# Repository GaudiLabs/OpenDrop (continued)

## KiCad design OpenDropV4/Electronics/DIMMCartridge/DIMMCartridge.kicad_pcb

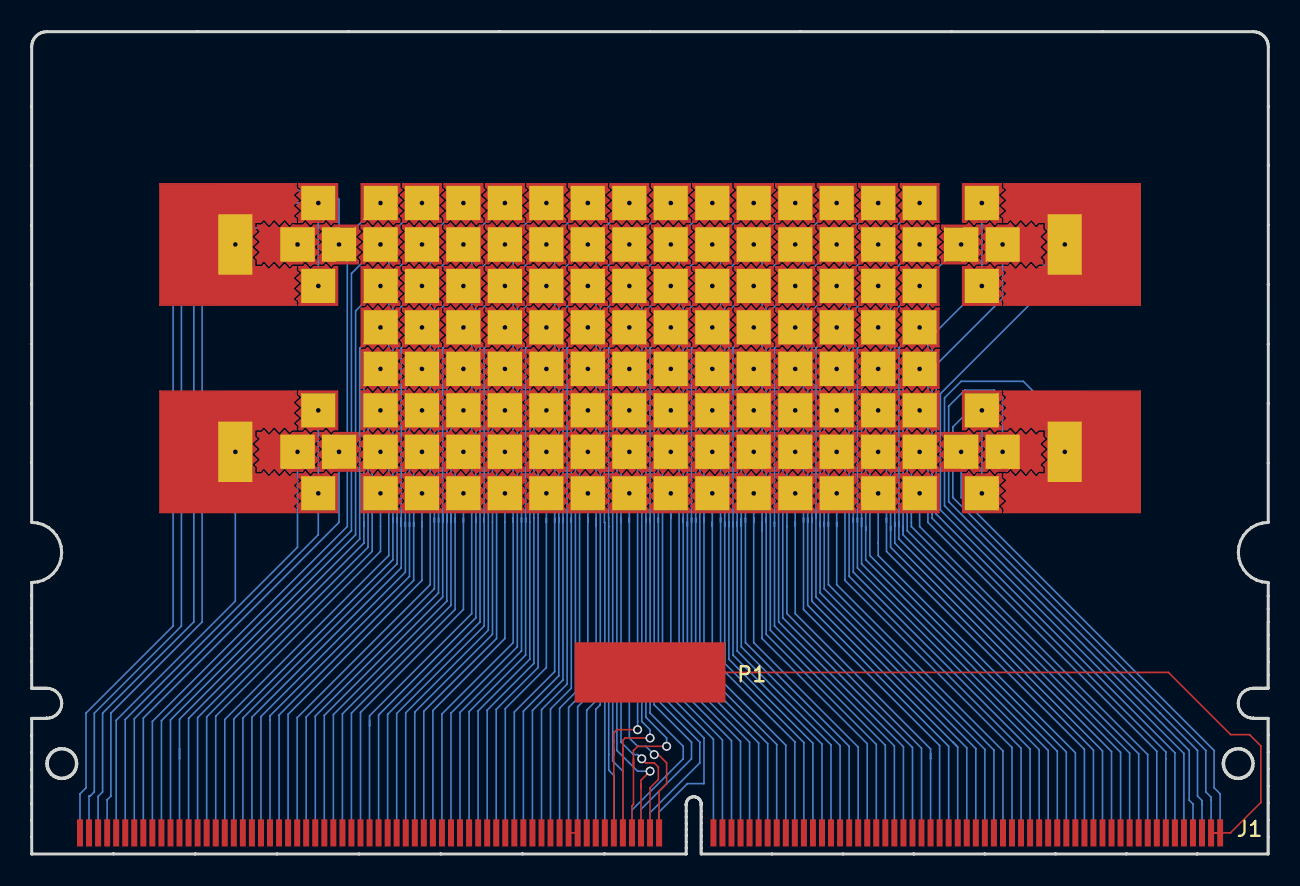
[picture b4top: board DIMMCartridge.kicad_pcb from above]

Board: 2 copper layers, 82.0 x 54.5 mm, 134 parts (0 on the bottom side), 130 nets.

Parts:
FLUXL_1_1, FLUXL_1_8, FLUXL_16_1, FLUXL_16_8: FX; FLUXPAD_2_75_4MIL_4_5_res1
FLUXL_1_2, FLUXL_1_7, FLUXL_16_2, FLUXL_16_7: FX; FLUXPAD_2_75_4MIL_4_5_res4
FLUXL_1_2b1, FLUXL_1_7b1, FLUXL_16_2b1, FLUXL_16_7b1: FX; FLUXPAD_2_75_4MIL_4_5_res5
FLUXL_1_3, FLUXL_1_6, FLUXL_16_3, FLUXL_16_6: FX; FLUXPAD_2_75_4MIL_4_5_res2
FLUXL_1_4, FLUXL_1_5, FLUXL_16_4, FLUXL_16_5: FX; FLUXPAD_2_75_4MIL_4_5_res3
FLUXL_2_1, FLUXL_15_8: FX; FLUXPAD_2_75_4MIL_4_5_topleft
FLUXL_2_2, FLUXL_2_7, FLUXL_3_2, FLUXL_3_3, FLUXL_3_4, FLUXL_3_5, FLUXL_3_6, FLUXL_3_7, FLUXL_4_2, FLUXL_4_3, FLUXL_4_4, FLUXL_4_5, FLUXL_4_6, FLUXL_4_7, FLUXL_5_2, FLUXL_5_3, FLUXL_5_4, FLUXL_5_5, FLUXL_5_6, FLUXL_5_7, FLUXL_6_2, FLUXL_6_3, FLUXL_6_4, FLUXL_6_5, FLUXL_6_6, FLUXL_6_7, FLUXL_7_2, FLUXL_7_3, FLUXL_7_4, FLUXL_7_5, FLUXL_7_6, FLUXL_7_7, FLUXL_8_2, FLUXL_8_3, FLUXL_8_4, FLUXL_8_5, FLUXL_8_6, FLUXL_8_7, FLUXL_9_2, FLUXL_9_3, FLUXL_9_4, FLUXL_9_5, FLUXL_9_6, FLUXL_9_7, FLUXL_10_2, FLUXL_10_3, FLUXL_10_4, FLUXL_10_5, FLUXL_10_6, FLUXL_10_7, FLUXL_11_2, FLUXL_11_3, FLUXL_11_4, FLUXL_11_5, FLUXL_11_6, FLUXL_11_7, FLUXL_12_2, FLUXL_12_3, FLUXL_12_4, FLUXL_12_5, FLUXL_12_6, FLUXL_12_7, FLUXL_13_2, FLUXL_13_3, FLUXL_13_4, FLUXL_13_5, FLUXL_13_6, FLUXL_13_7, FLUXL_14_2, FLUXL_14_3, FLUXL_14_4, FLUXL_14_5, FLUXL_14_6, FLUXL_14_7, FLUXL_15_2, FLUXL_15_7: FX; FLUXPAD_2_75_4MIL_4_5
FLUXL_2_3, FLUXL_2_4, FLUXL_2_5, FLUXL_2_6, FLUXL_15_3, FLUXL_15_4, FLUXL_15_5, FLUXL_15_6: FX; FLUXPAD_2_75_4MIL_4_5_side
FLUXL_2_8, FLUXL_15_1: FX; FLUXPAD_2_75_4MIL_4_5_topright
FLUXL_3_1, FLUXL_3_8, FLUXL_4_1, FLUXL_4_8, FLUXL_5_1, FLUXL_5_8, FLUXL_6_1, FLUXL_6_8, FLUXL_7_1, FLUXL_7_8, FLUXL_8_1, FLUXL_8_8, FLUXL_9_1, FLUXL_9_8, FLUXL_10_1, FLUXL_10_8, FLUXL_11_1, FLUXL_11_8, FLUXL_12_1, FLUXL_12_8, FLUXL_13_1, FLUXL_13_8, FLUXL_14_1, FLUXL_14_8: FX; FLUXPAD_2_75_4MIL_4_5_top
J1: Mini_Dimm_244; Mini_Dimm_Cartridge_06_244
P1: V_GND; Pad_4mm_10mm

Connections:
unnamed: FLUXL_1_1.1, J1.244
unnamed: FLUXL_1_2.1, FLUXL_1_2b1.1, J1.243
unnamed: FLUXL_1_3.1, J1.242
unnamed: FLUXL_1_4.1, J1.241
unnamed: FLUXL_1_5.1, J1.240
unnamed: FLUXL_1_6.1, J1.239
unnamed: FLUXL_1_7.1, FLUXL_1_7b1.1, J1.238
unnamed: FLUXL_1_8.1, J1.237
unnamed: FLUXL_2_1.1, J1.236
unnamed: FLUXL_2_2.1, J1.235
unnamed: FLUXL_2_3.1, J1.234
unnamed: FLUXL_2_4.1, J1.233
unnamed: FLUXL_2_5.1, J1.232
unnamed: FLUXL_2_6.1, J1.231
unnamed: FLUXL_2_7.1, J1.230
unnamed: FLUXL_2_8.1, J1.229
unnamed: FLUXL_3_1.1, J1.228
unnamed: FLUXL_3_2.1, J1.227
unnamed: FLUXL_3_3.1, J1.226
unnamed: FLUXL_3_4.1, J1.225
unnamed: FLUXL_3_5.1, J1.224
unnamed: FLUXL_3_6.1, J1.223
unnamed: FLUXL_3_7.1, J1.222
unnamed: FLUXL_3_8.1, J1.221
unnamed: FLUXL_4_1.1, J1.220
unnamed: FLUXL_4_2.1, J1.219
unnamed: FLUXL_4_3.1, J1.218
unnamed: FLUXL_4_4.1, J1.217
unnamed: FLUXL_4_5.1, J1.216
unnamed: FLUXL_4_6.1, J1.215
unnamed: FLUXL_4_7.1, J1.214
unnamed: FLUXL_4_8.1, J1.213
unnamed: FLUXL_5_1.1, J1.212
unnamed: FLUXL_5_2.1, J1.211
unnamed: FLUXL_5_3.1, J1.210
unnamed: FLUXL_5_4.1, J1.209
unnamed: FLUXL_5_5.1, J1.208
unnamed: FLUXL_5_6.1, J1.207
unnamed: FLUXL_5_7.1, J1.206
unnamed: FLUXL_5_8.1, J1.205
unnamed: FLUXL_6_1.1, J1.204
unnamed: FLUXL_6_2.1, J1.203
unnamed: FLUXL_6_3.1, J1.202
unnamed: FLUXL_6_4.1, J1.201
unnamed: FLUXL_6_5.1, J1.200
unnamed: FLUXL_6_6.1, J1.199
unnamed: FLUXL_6_7.1, J1.198
unnamed: FLUXL_6_8.1, J1.197
unnamed: FLUXL_7_1.1, J1.196
unnamed: FLUXL_7_2.1, J1.195
unnamed: FLUXL_7_3.1, J1.194
unnamed: FLUXL_7_4.1, J1.193
unnamed: FLUXL_7_5.1, J1.192
unnamed: FLUXL_7_6.1, J1.191
unnamed: FLUXL_7_7.1, J1.190
unnamed: FLUXL_7_8.1, J1.189
unnamed: FLUXL_8_1.1, J1.188
unnamed: FLUXL_8_2.1, J1.187
unnamed: FLUXL_8_3.1, J1.186
unnamed: FLUXL_8_4.1, J1.185
unnamed: FLUXL_8_5.1, J1.184
unnamed: FLUXL_8_6.1, J1.63
unnamed: FLUXL_8_7.1, J1.64
unnamed: FLUXL_8_8.1, J1.65
unnamed: FLUXL_9_1.1, J1.60
unnamed: FLUXL_9_2.1, J1.61
unnamed: FLUXL_9_3.1, J1.62
unnamed: FLUXL_9_4.1, J1.183
unnamed: FLUXL_9_5.1, J1.182
unnamed: FLUXL_9_6.1, J1.181
unnamed: FLUXL_9_7.1, J1.180
unnamed: FLUXL_9_8.1, J1.179
unnamed: FLUXL_10_1.1, J1.178
unnamed: FLUXL_10_2.1, J1.177
unnamed: FLUXL_10_3.1, J1.176
unnamed: FLUXL_10_4.1, J1.175
unnamed: FLUXL_10_5.1, J1.174
unnamed: FLUXL_10_6.1, J1.173
unnamed: FLUXL_10_7.1, J1.172
unnamed: FLUXL_10_8.1, J1.171
unnamed: FLUXL_11_1.1, J1.170
unnamed: FLUXL_11_2.1, J1.169
unnamed: FLUXL_11_3.1, J1.168
unnamed: FLUXL_11_4.1, J1.167
unnamed: FLUXL_11_5.1, J1.166
unnamed: FLUXL_11_6.1, J1.165
unnamed: FLUXL_11_7.1, J1.164
unnamed: FLUXL_11_8.1, J1.163
unnamed: FLUXL_12_1.1, J1.162
unnamed: FLUXL_12_2.1, J1.161
unnamed: FLUXL_12_3.1, J1.160
unnamed: FLUXL_12_4.1, J1.159
unnamed: FLUXL_12_5.1, J1.158
unnamed: FLUXL_12_6.1, J1.157
unnamed: FLUXL_12_7.1, J1.156
unnamed: FLUXL_12_8.1, J1.155
unnamed: FLUXL_13_1.1, J1.154
unnamed: FLUXL_13_2.1, J1.153
unnamed: FLUXL_13_3.1, J1.152
unnamed: FLUXL_13_4.1, J1.151
unnamed: FLUXL_13_5.1, J1.150
unnamed: FLUXL_13_6.1, J1.149
unnamed: FLUXL_13_7.1, J1.148
unnamed: FLUXL_13_8.1, J1.147
unnamed: FLUXL_14_1.1, J1.146
unnamed: FLUXL_14_2.1, J1.145
unnamed: FLUXL_14_3.1, J1.144
unnamed: FLUXL_14_4.1, J1.143
unnamed: FLUXL_14_5.1, J1.142
unnamed: FLUXL_14_6.1, J1.141
unnamed: FLUXL_14_7.1, J1.140
unnamed: FLUXL_14_8.1, J1.139
unnamed: FLUXL_15_1.1, J1.138
unnamed: FLUXL_15_2.1, J1.137
unnamed: FLUXL_15_3.1, J1.136
unnamed: FLUXL_15_4.1, J1.135
unnamed: FLUXL_15_5.1, J1.134
unnamed: FLUXL_15_6.1, J1.133
unnamed: FLUXL_15_7.1, J1.132
unnamed: FLUXL_15_8.1, J1.131
unnamed: FLUXL_16_1.1, J1.130
unnamed: FLUXL_16_2.1, FLUXL_16_2b1.1, J1.129
unnamed: FLUXL_16_3.1, J1.128
unnamed: FLUXL_16_4.1, J1.127
unnamed: FLUXL_16_5.1, J1.126
unnamed: FLUXL_16_6.1, J1.125
unnamed: FLUXL_16_7.1, FLUXL_16_7b1.1, J1.124
unnamed: FLUXL_16_8.1, J1.123
unnamed: J1.55, J1.56
V_GND: J1.121, J1.122, P1.1

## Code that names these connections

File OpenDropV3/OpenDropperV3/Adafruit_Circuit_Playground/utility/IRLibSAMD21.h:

/* IRLibSAMD21.h
 * Part of IRLib Library for Arduino receiving, decoding, and sending
 * infrared signals. See COPYRIGHT.txt and LICENSE.txt for more information.
 *
 * This type of content is normally stored in IRLibHardware.h but we have 
 * moved at her because the SAMD21 support is significantly different than the
 * AVR 8-bit hardware support. Separating it out into a separate file
 * will make it easier to include comments and to maintain the code.
 */

/* This file provides hardware support for the SAMD21G18A processor or as we 
 * will refer to it simply as SAMD 21. This processor is used in the Arduino Zero, 
 * Arduino M0, Arduino M0 Pro, and the Adafruit Feather M0 series boards as well as
 * the upcoming Adafruit Circuit Playground Express.
 * Most of the code has been adapted from messages on the Arduino.cc support forum 
 * and from the code at:
 *	https://github.com/manitou48/ZERO/tree/master/IRtest
 * Receiving is supported through all three receiver classes. As you would expect 
 * the IRrecvLoop class can be used with any available input pin. The IRrecvPCI and 
 * IRfrequency classes can be used on any pin that supports "attachInterrupt()". 
 * Specifically that means everything except pin 4 on the Arduino Zero. And everything 
 * except pin 2 on the boards from Arduino.org such as the Arduino M0, M0 Pro, and 
 * Zero Pro. For details on supported pins see these links:
 *	https://www.arduino.cc/en/Reference/AttachInterrupt
 *	http://www.arduino.org/learning/reference/AttachInterrupt
 * Note that although we support Arduino.org hardware, you should only use the 
 * Arduino.cc IDE for compiling your sketches.
 * Both sending and receiving use GCLK0 even though GCLK0-GCLK3 are generally reserved
 * the Arduino infrastructure. However we are using the default 48 MHz clock source
 * and a divisor of "1" so we aren't changing any of the GCLK0 set up. It's therefore
 * safe to use.
 * The IRrecv receiver class using a 50 microsecond timer interrupt is also supported. 
 * It defaults to using hardware timer TC3 however TC4 and TC5 can also be used in case 
 * of conflicts with other libraries. The IRrecv and IRrecvLoop classes should be able to use
 * any available input pin. Note that all of our example sketches used pin 2 for 
 * receiver and pin 3 for frequency measurement. However pin 2 is not available for PCI 
 * interrupts on the Arduino.org platforms and neither 2 nor 3 are available on the 
 * Adafruit Feather M0 platforms. We are recommending using 5 and 6 for receiving and
 * frequency measurement respectively.
 * For sending, you can use any pin that supports PWM on your particular 
 * platform. On Arduino Zero that means pins 3, 4, 5, 6, 8, 9, 10, 11, 12, or 13.
 * Additionally Arduino M0 Pro adds pins 2 and 7 to that list. In all cases the default
 * output pin is 9. The code automatically selects TCC0 or TCC1 based on pin number
 * as needed. It has been tested at frequencies of 36, 38, 39, 40 and 57 which
 * are the frequencies of our supported protocols.
 * As of this release the code has been tested on Arduino Zero, Arduino M0 Pro, and 
 * Adafruit Feather M0 BLE version.
 */
#ifndef IRLibSAMD21_h
#define IRLibSAMD21_h
/*
 * This section contains user changeable values. You can probably stick with the defaults
 * but if there are hardware conflicts with other libraries, you can change these values.
 */
//Choose PWM output pin number from among the following
//Un-comment only one of these. 
//#define IR_SEND_PWM_PIN 2
//#define IR_SEND_PWM_PIN 3
//#define IR_SEND_PWM_PIN 4
//#define IR_SEND_PWM_PIN 5
//#define IR_SEND_PWM_PIN 6
//#define IR_SEND_PWM_PIN 7
//#define IR_SEND_PWM_PIN 8
//#define IR_SEND_PWM_PIN 9
//#define IR_SEND_PWM_PIN 10
//#define IR_SEND_PWM_PIN 11
#define IR_SEND_PWM_PIN 12
//#define IR_SEND_PWM_PIN 13
//Override default for Adafruit Circuit Playground Express
#ifdef ADAFRUIT_CIRCUITPLAYGROUND_M0 
  #define IR_SEND_PWM_PIN 25
#endif
//Choose which timer counter to use for the 50 microsecond interrupt
//Un-comment only one of these.
#define IR_TCn 3
//#define IR_TCn 4
//#define IR_TCn 5

/*
 * Everything below this point should not be changed. It computes needed defines
 * based on the user set values above.
 */

// Saves us a lot of typing when synchronizing
#define syncTC   while (IR_TCx->COUNT16.STATUS.bit.SYNCBUSY)
#define syncGCLK while (GCLK->STATUS.bit.SYNCBUSY)

#if defined(ARDUINO_SAMD_FEATHER_M0)
  #if ( (IR_SEND_PWM_PIN<5) || (IR_SEND_PWM_PIN==7) || (IR_SEND_PWM_PIN==8) )
    #error "Pin unsupported on Adafruit Feather M0"
  #endif
#endif

//Pins 8 and 9 use TCC1 and all others use TCC0
#if ( (IR_SEND_PWM_PIN==8) || (IR_SEND_PWM_PIN==9) )
  #define IR_TCCx TCC1
#else
  #define IR_TCCx TCC0
#endif

//Although there are 8 WO there are only 4 CC
#define CC4 CC0
#define CC5 CC1
#define CC6 CC2
#define CC7 CC3

//Set other values based on pin number
#if (IR_SEND_PWM_PIN==2)
  //NOTE: Arduino M0 Pro only
  #if defined(ARDUINO_SAM_ZERO)
    //PA08 E:TCC0-WO[0] F:TCC1-WO[2]
    #define IR_MUX_EF PORT_PMUX_PMUXE_E
    #define IR_CCx CC0
    #define IR_CCn 0
  #else
    #error "Pin 2 only available on Arduino M0 Pro"
  #endif
#elif (IR_SEND_PWM_PIN==3)
  //PA09 E:TCC0-WO[1] F:TCC1-WO[3]
  #define IR_MUX_EF PORT_PMUX_PMUXO_E 
  #define IR_CCx CC1
  #define IR_CCn 1
#elif (IR_SEND_PWM_PIN==4)
  //Arduino M0 Pro swaps pins 2 and 4
  #if(ARDUINO_SAM_ZERO)
    //Arduino M0 Pro
    //PA09 E:TC3-WO[0] F:TCC0-WO[4]
    #define IR_MUX_EF PORT_PMUX_PMUXE_F 
    #define IR_CCx CC4
    #define IR_CCn 4
  #else
    //Arduino Zero
    //PA08 E:TCC0-WO[0] F:TCC1-WO[2]
    #define IR_MUX_EF PORT_PMUX_PMUXE_E
    #define IR_CCx CC0
    #define IR_CCn 0
  #endif
#elif (IR_SEND_PWM_PIN==5)
  //PA15 E:TC3-WO[1] F:TCC0-WO[5]
  #define IR_MUX_EF PORT_PMUX_PMUXO_F
  #define IR_CCx CC5
  #define IR_CCn 5
#elif (IR_SEND_PWM_PIN==6)
  //PA20 E:TC7-WO[0] F:TCC0-WO[6]
  #define IR_MUX_EF PORT_PMUX_PMUXE_F
  #define IR_CCx CC6
  #define IR_CCn 6
#elif (IR_SEND_PWM_PIN==7)
  //NOTE: Arduino M0 Pro only
  #if defined(ARDUINO_SAM_ZERO)
    //PA08 E:TC7-WO[1] F:TCC0-WO[7]
    #define IR_MUX_EF PORT_PMUX_PMUXO_F
    #define IR_CCx CC7
    #define IR_CCn 7
  #else
    #error "Pin 7 only available on Arduino M0 Pro"
  #endif
#elif (IR_SEND_PWM_PIN==8)
  //PA06 E:TCC1-WO[0] F:--
  #define IR_MUX_EF PORT_PMUX_PMUXE_E 
  #define IR_CCx CC0
  #define IR_CCn 0
#elif (IR_SEND_PWM_PIN==9)
  //PA07 E:TCC1-WO[1] F:--
  #define IR_MUX_EF PORT_PMUX_PMUXO_E 
  #define IR_CCx CC1
  #define IR_CCn 1
#elif (IR_SEND_PWM_PIN==10)
  //PA18 E:TC3-WO[0] F:TCC0-WO[2]
  #define IR_MUX_EF PORT_PMUX_PMUXE_F
  #define IR_CCx CC2
  #define IR_CCn 2
#elif (IR_SEND_PWM_PIN==11)
  //PA16 E:TCC2-WO[0] F:TCC0-WO[6]
  #define IR_MUX_EF PORT_PMUX_PMUXE_F 
  #define IR_CCx CC6
  #define IR_CCn 6
#elif (IR_SEND_PWM_PIN==12)
  //PA19 E:TC3-WO[1] F:TCC0-WO[3]
  #define IR_MUX_EF PORT_PMUX_PMUXO_F
  #define IR_CCx CC3
  #define IR_CCn 3
#elif (IR_SEND_PWM_PIN==13)
  //PA17 E:TCC2-WO[1] F:TCC0-WO[7]
  #define IR_MUX_EF PORT_PMUX_PMUXO_F 
  #define IR_CCx CC7
  #define IR_CCn 7
#elif (IR_SEND_PWM_PIN==25)//Adafruit Circuit Playground Express only
  //PA23 E:TC4-WO[1] F:TCC0-WO[5]
  #define IR_MUX_EF PORT_PMUX_PMUXO_F 
  #define IR_CCx CC5
  #define IR_CCn 5
#else 
  #error "Invalid SAMD21 PWM pin"
#endif

// Turns PWM on and off after already set up
#define IR_SEND_PWM_START {IR_TCCx->CTRLA.reg |= TCC_CTRLA_ENABLE;\
  while (IR_TCCx->SYNCBUSY.bit.ENABLE);}
#define IR_SEND_MARK_TIME(time)  IRLibDelayUSecs(time)
#define IR_SEND_PWM_STOP {IR_TCCx->CTRLA.reg &= ~TCC_CTRLA_ENABLE;\
  while (IR_TCCx->SYNCBUSY.bit.ENABLE);}
#define IR_SEND_CONFIG_KHZ(val) initializeSAMD21PWM(val);

/* These are the definitions for setting up the 50 microsecond
 * timer interrupt for the IRrecv class. 
 */
#if (IR_TCn==3)
  #define IR_TCx   TC3
  #define IR_GCM   GCM_TCC2_TC3
  #define IR_RECV_INTR_NAME void TC3_Handler()
  #define IR_IRQ   TC3_IRQn
#elif (IR_TCn==4)
  #define IR_TCx   TC4
  #define IR_GCM   GCM_TC4_TC5
  #define IR_RECV_INTR_NAME void TC4_Handler()
  #define IR_IRQ   TC4_IRQn
#elif (IR_TCn==5)
  #define IR_TCx   TC5
  #define IR_GCM   GCM_TC4_TC5
  #define IR_RECV_INTR_NAME void TC5_Handler()
  #define IR_IRQ   TC5_IRQn
#else
  #error "Invalid IR_TCn value"
#endif

#define IR_RECV_ENABLE_INTR ({NVIC_EnableIRQ(IR_IRQ);\
    IR_TCx->COUNT16.INTENSET.reg = TC_INTENSET_OVF;\
    IR_TCx->COUNT16.CTRLA.reg |= TC_CTRLA_ENABLE; syncTC;})
#define IR_RECV_DISABLE_INTR  IR_TCx->COUNT16.INTENCLR.reg = TC_INTENCLR_OVF;  
#define IR_RECV_CONFIG_TICKS() initializeSAMD21timerInterrupt()

//Clear interrupt
#define IR_CLEAR_INTERRUPT 	IR_TCx->COUNT16.INTFLAG.bit.MC0 = 1;

//prototypes
void initializeSAMD21PWM(uint16_t khz);
void initializeSAMD21timerInterrupt(void);

#endif //IRLibSAMD21_h
